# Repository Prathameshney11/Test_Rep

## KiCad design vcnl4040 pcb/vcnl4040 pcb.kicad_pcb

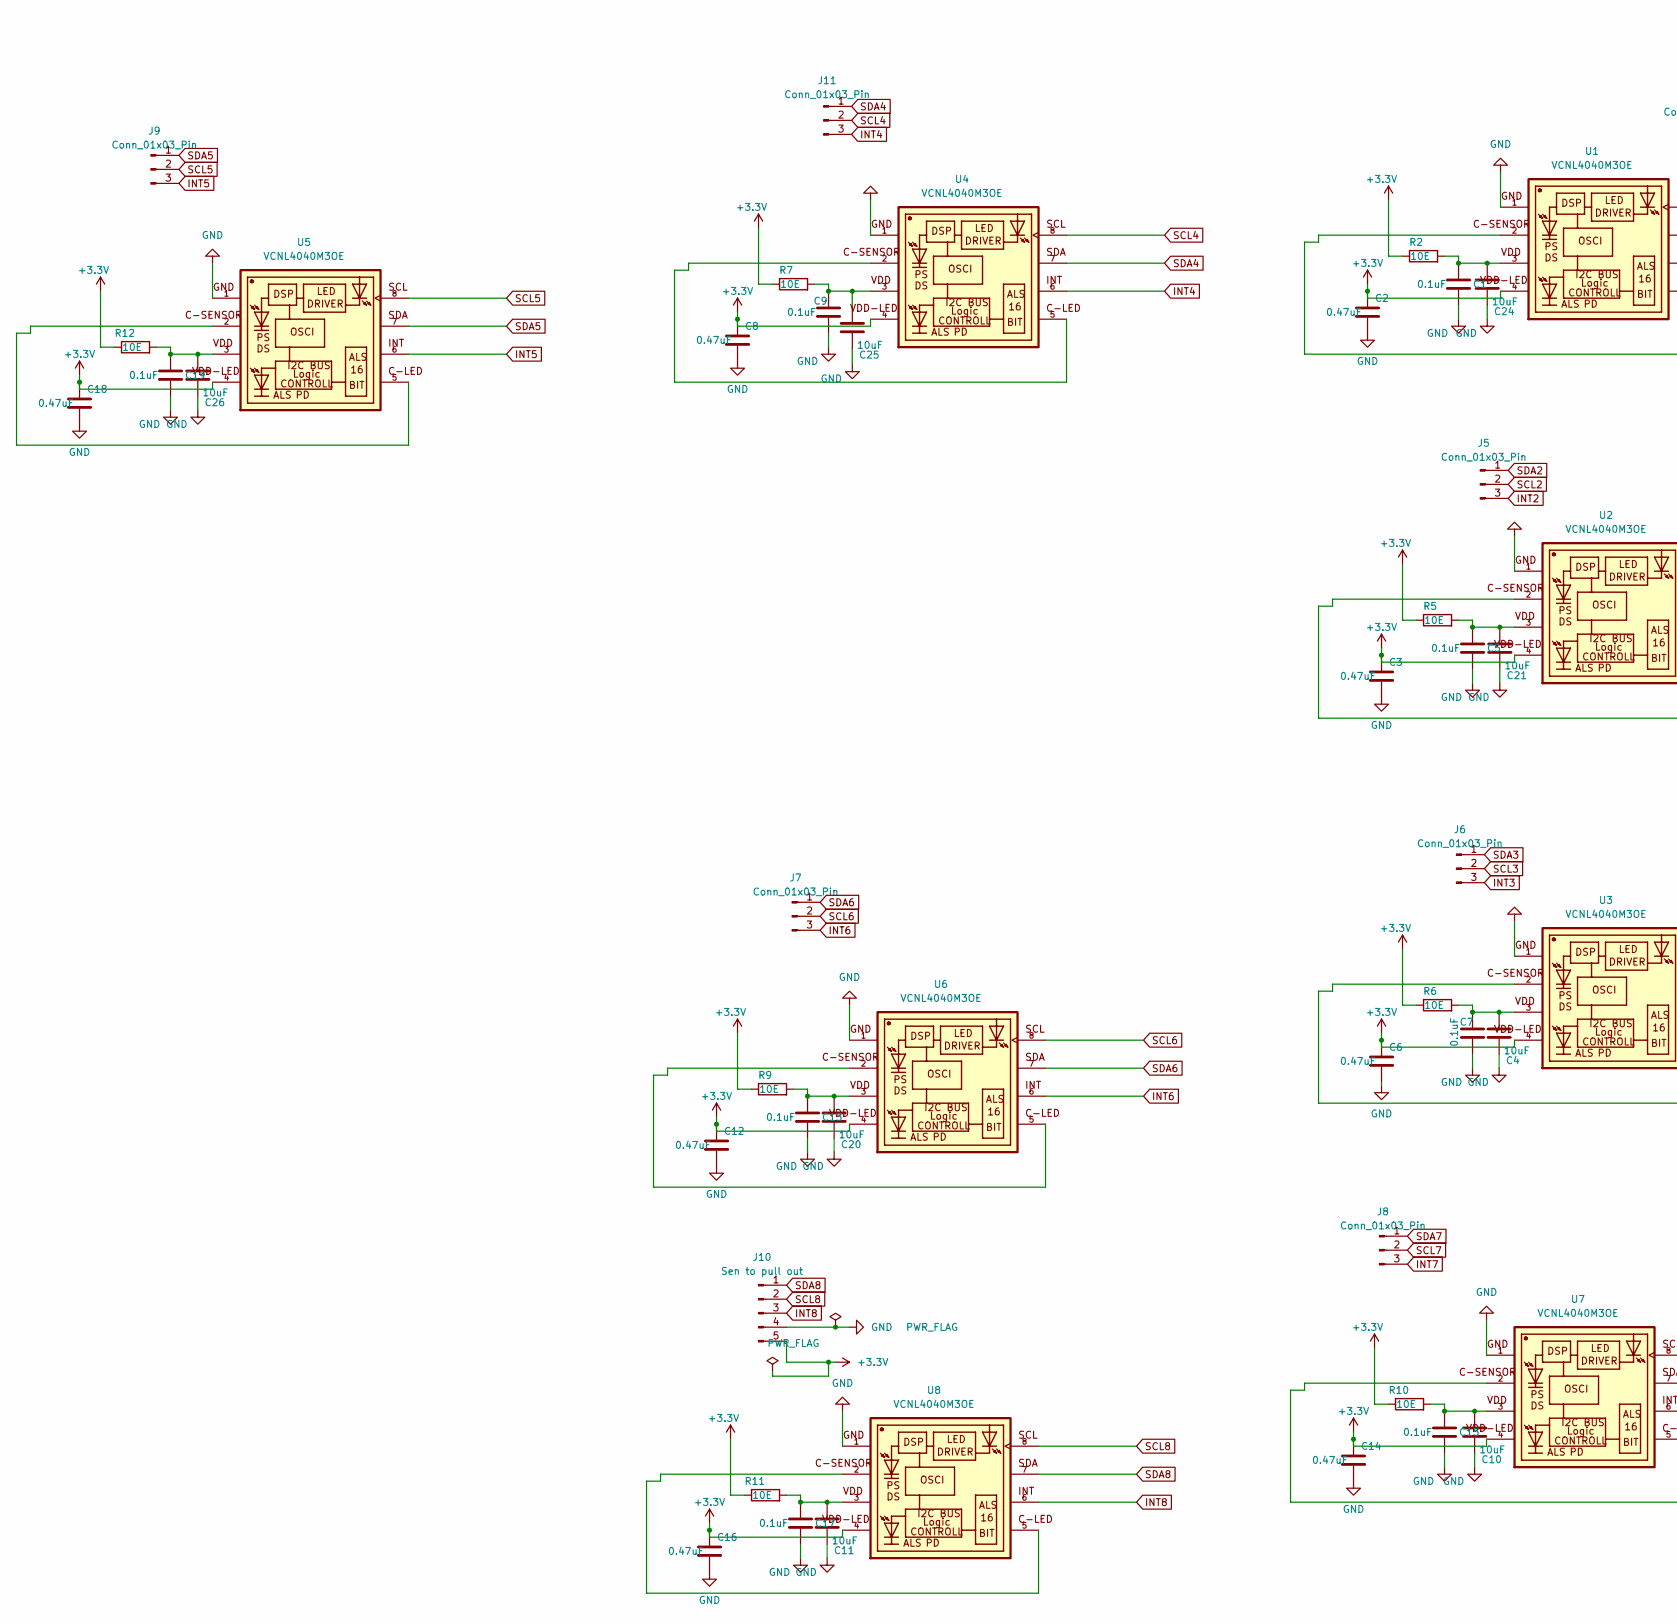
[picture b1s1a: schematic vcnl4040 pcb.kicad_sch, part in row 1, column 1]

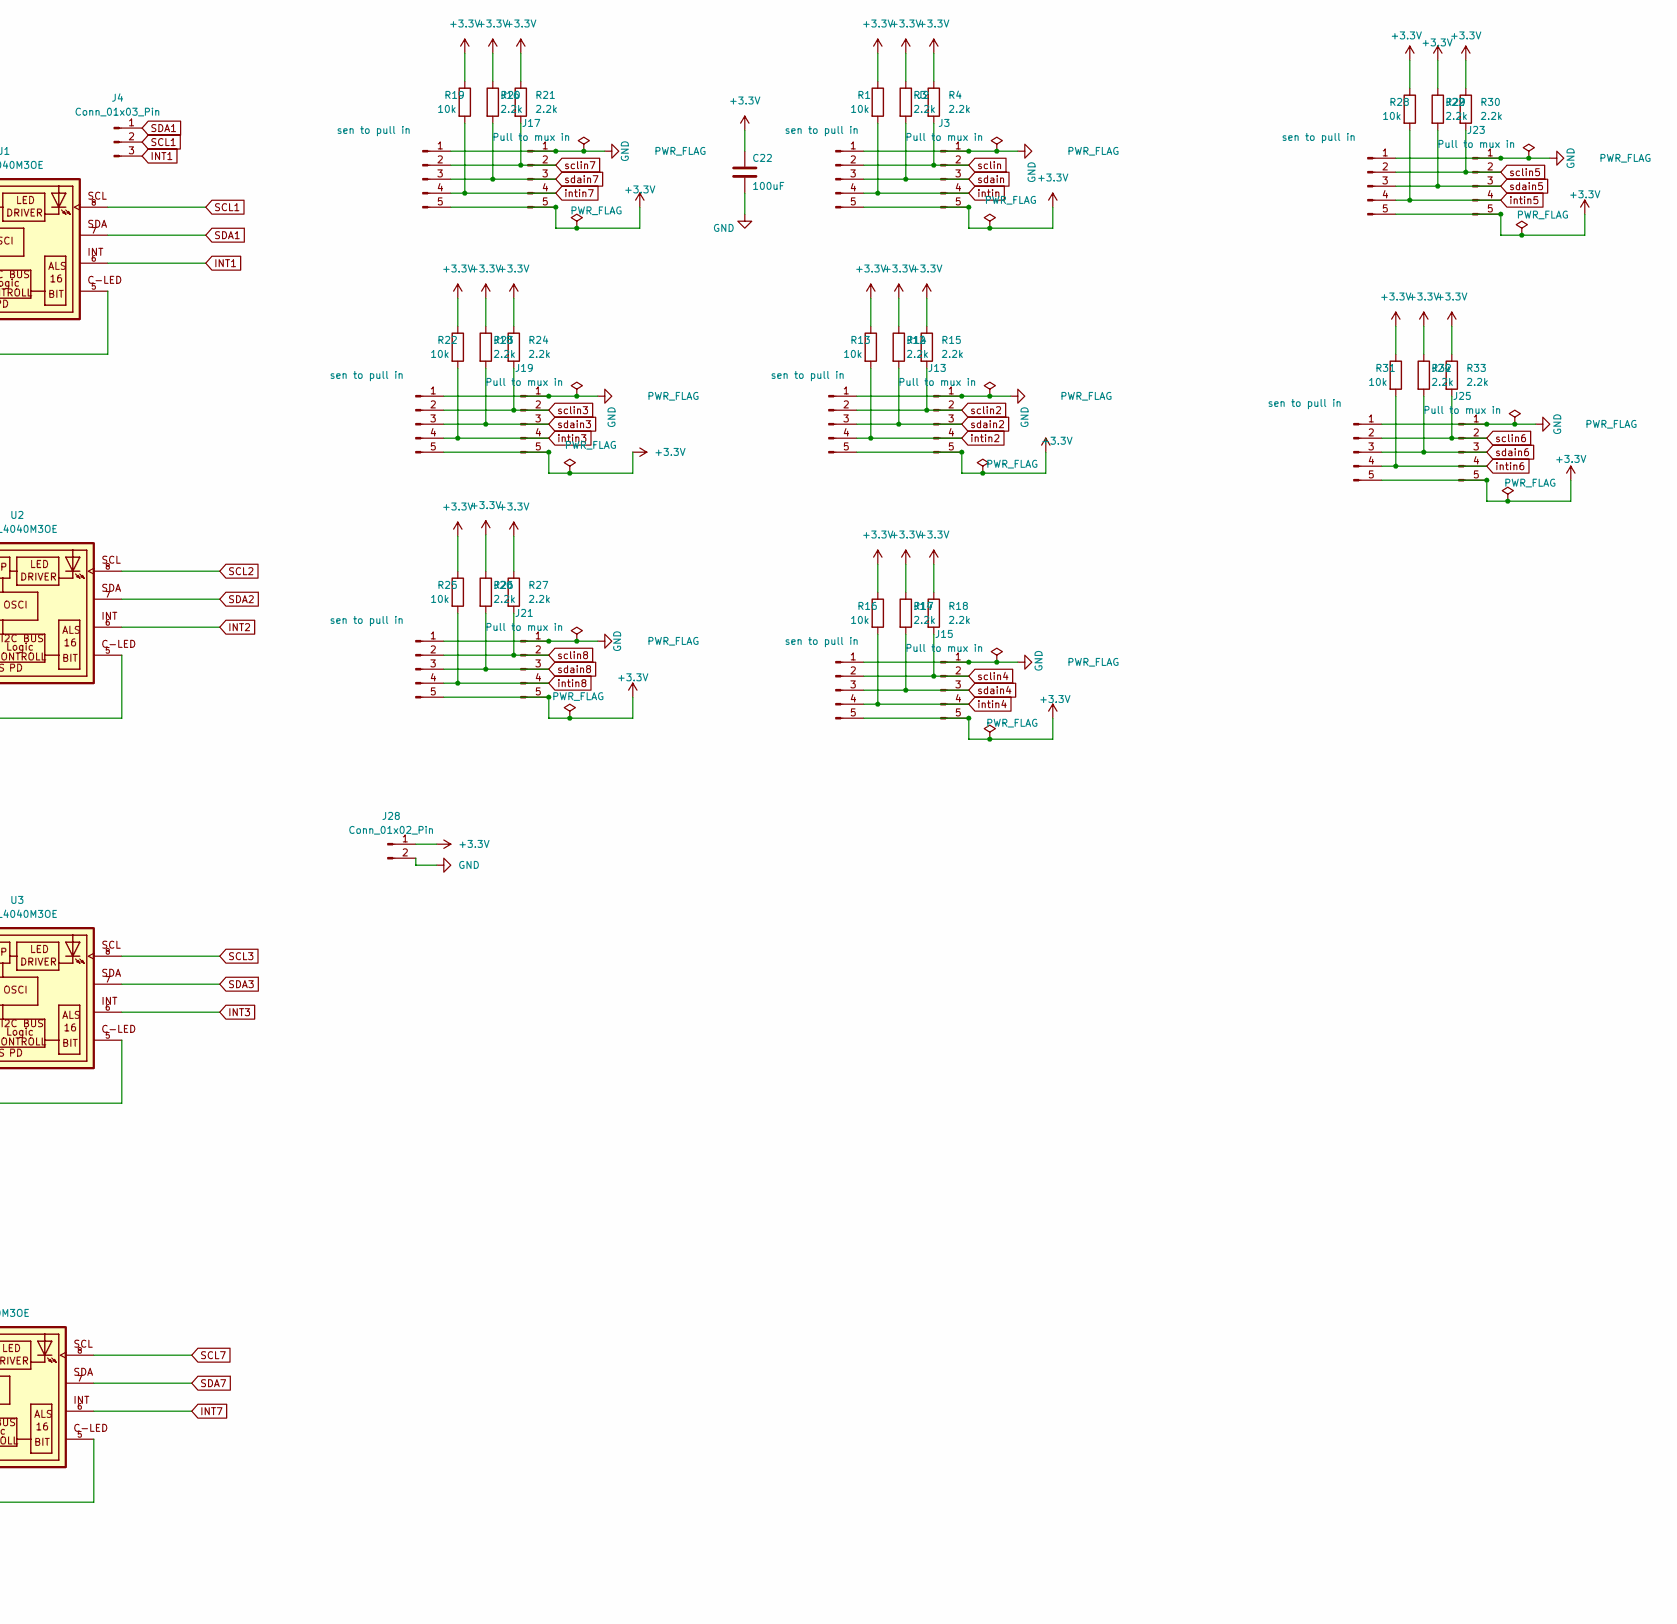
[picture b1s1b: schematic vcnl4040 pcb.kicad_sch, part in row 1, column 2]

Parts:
C1, C5, C7, C9, C13, C15, C17, C19: 0.1uF; C_0805_2012Metric_Pad1.18x1.45mm_HandSolder
C2, C3, C6, C8, C12, C14, C16, C18: 0.47uF; C_0805_2012Metric_Pad1.18x1.45mm_HandSolder
C4, C10, C11, C20, C21, C24, C25, C26: 10uF; C_0805_2012Metric_Pad1.18x1.45mm_HandSolder
C22: 100uF; CP_Radial_D5.0mm_P2.00mm
J2, J12, J14, J16, J18, J20, J22, J24: sen to pull in; PinHeader_1x05_P2.54mm_Vertical
J3, J13, J15, J17, J19, J21, J23, J25: Pull to mux in; PinHeader_1x05_P2.54mm_Vertical
J4, J5, J6, J7, J8, J9, J11: Conn_01x03_Pin; PinHeader_1x03_P2.54mm_Vertical
J10: Sen to pull out; PinHeader_1x05_P2.54mm_Vertical
J28: Conn_01x02_Pin; TerminalBlock_bornier-2_P5.08mm
R1, R13, R16, R19, R22, R25, R28, R31: 10k; R_0805_2012Metric_Pad1.20x1.40mm_HandSolder
R2, R5, R6, R7, R9, R10, R11, R12: 10E; R_0805_2012Metric_Pad1.20x1.40mm_HandSolder
R3, R4, R14, R15, R17, R18, R20, R21, R23, R24, R26, R27, R29, R30, R32, R33: 2.2k; R_0805_2012Metric_Pad1.20x1.40mm_HandSolder
U1, U2, U3, U4, U5, U6, U7, U8: VCNL4040M3OE; VISHAY_VCNL4040_4X2X1.1

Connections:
+3.3V: C2.1, C3.1, C6.1, C8.1, C12.1, C14.1, C16.1, C18.1, C22.1, J2.5, J3.5, J10.5, J12.5, J13.5, J14.5, J15.5, J16.5, J17.5, J18.5, J19.5, J20.5, J21.5, J22.5, J23.5, J24.5, J25.5, J28.1, R1.1, R2.1, R3.1, R4.1, R5.1, R6.1, R7.1, R9.1, R10.1, R11.1, R12.1, R13.1, R14.1, R15.1, R16.1, R17.1, R18.1, R19.1, R20.1, R21.1, R22.1, R23.1, R24.1, R25.1, R26.1, R27.1, R28.1, R29.1, R30.1, R31.1, R32.1, R33.1, U1.4, U2.4, U3.4, U4.4, U5.4, U6.4, U7.4, U8.4
GND: C1.2, C2.2, C3.2, C4.2, C5.2, C6.2, C7.2, C8.2, C9.2, C10.2, C11.2, C12.2, C13.2, C14.2, C15.2, C16.2, C17.2, C18.2, C19.2, C20.2, C21.2, C22.2, C24.2, C25.2, C26.2, J2.1, J3.1, J10.4, J12.1, J13.1, J14.1, J15.1, J16.1, J17.1, J18.1, J19.1, J20.1, J21.1, J22.1, J23.1, J24.1, J25.1, J28.2, U1.1, U2.1, U3.1, U4.1, U5.1, U6.1, U7.1, U8.1
INT1: J4.3, U1.6
INT2: J5.3, U2.6
INT3: J6.3, U3.6
INT4: J11.3, U4.6
INT5: J9.3, U5.6
INT6: J7.3, U6.6
INT7: J8.3, U7.6
INT8: J10.3, U8.6
unnamed: C1.1, C24.1, R2.2, U1.3
unnamed: C4.1, C7.1, R6.2, U3.3
unnamed: C10.1, C15.1, R10.2, U7.3
unnamed: C11.1, C17.1, R11.2, U8.3
unnamed: C13.1, C20.1, R9.2, U6.3
unnamed: C19.1, C26.1, R12.2, U5.3
unnamed: C5.1, C21.1, R5.2, U2.3
unnamed: C9.1, C25.1, R7.2, U4.3
unnamed: U1.2, U1.5
unnamed: U2.2, U2.5
unnamed: U3.2, U3.5
unnamed: U4.2, U4.5
unnamed: U5.2, U5.5
unnamed: U6.2, U6.5
unnamed: U7.2, U7.5
unnamed: U8.2, U8.5
SCL1: J4.2, U1.8
SCL2: J5.2, U2.8
SCL3: J6.2, U3.8
SCL4: J11.2, U4.8
SCL5: J9.2, U5.8
SCL6: J7.2, U6.8
SCL7: J8.2, U7.8
SCL8: J10.2, U8.8
SDA1: J4.1, U1.7
SDA2: J5.1, U2.7
SDA3: J6.1, U3.7
SDA4: J11.1, U4.7
SDA5: J9.1, U5.7
SDA6: J7.1, U6.7
SDA7: J8.1, U7.7
SDA8: J10.1, U8.7
intin: J2.4, J3.4, R1.2
intin2: J12.4, J13.4, R13.2
intin3: J18.4, J19.4, R22.2
intin4: J14.4, J15.4, R16.2
intin5: J22.4, J23.4, R28.2
intin6: J24.4, J25.4, R31.2
intin7: J16.4, J17.4, R19.2
intin8: J20.4, J21.4, R25.2
sclin: J2.2, J3.2, R4.2
sclin2: J12.2, J13.2, R15.2
sclin3: J18.2, J19.2, R24.2
sclin4: J14.2, J15.2, R18.2
sclin5: J22.2, J23.2, R30.2
sclin6: J24.2, J25.2, R33.2
sclin7: J16.2, J17.2, R21.2
sclin8: J20.2, J21.2, R27.2
sdain: J2.3, J3.3, R3.2
sdain2: J12.3, J13.3, R14.2
sdain3: J18.3, J19.3, R23.2
sdain4: J14.3, J15.3, R17.2
sdain5: J22.3, J23.3, R29.2
sdain6: J24.3, J25.3, R32.2
sdain7: J16.3, J17.3, R20.2
sdain8: J20.3, J21.3, R26.2

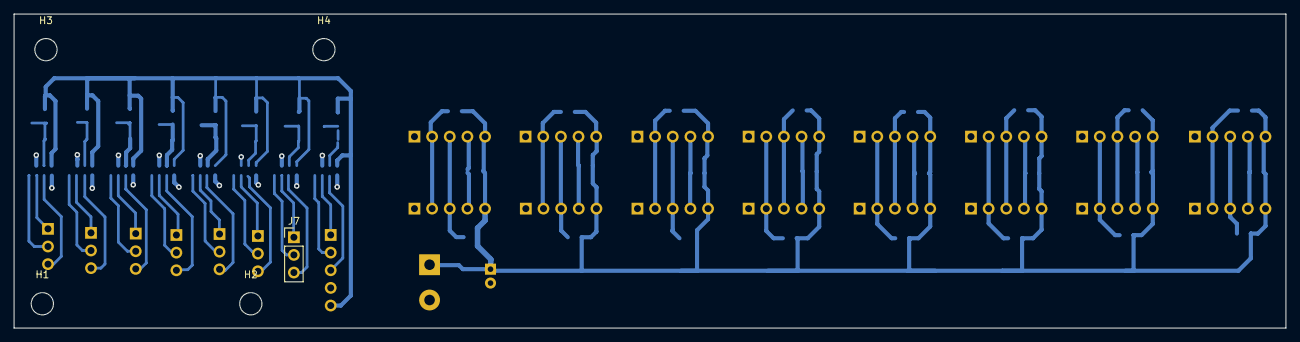
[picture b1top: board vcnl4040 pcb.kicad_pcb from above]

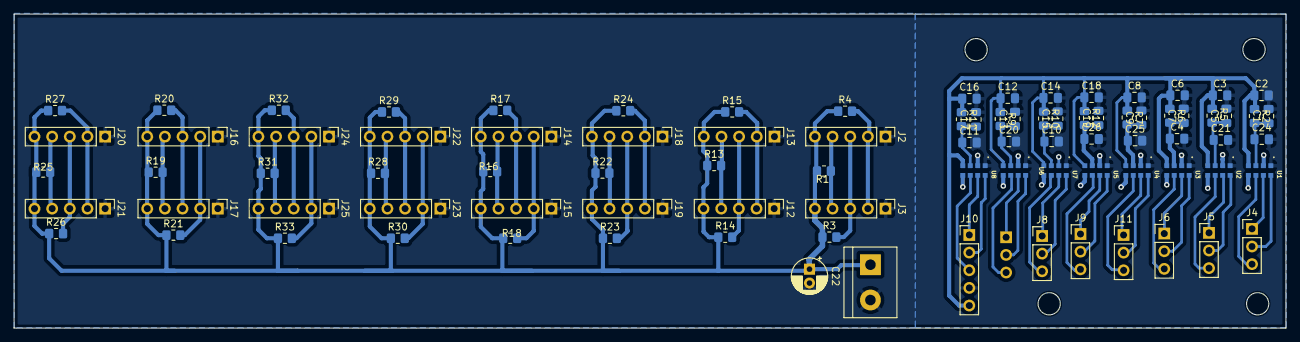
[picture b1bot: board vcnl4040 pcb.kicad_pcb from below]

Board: 2 copper layers, 183.0 x 45.2 mm, 94 parts (89 on the bottom side), 66 nets.

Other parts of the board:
H1, H2, H3, H4: MountingHole; MountingHole_3.2mm_M3

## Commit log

2024-08-30 Added PCB Files
